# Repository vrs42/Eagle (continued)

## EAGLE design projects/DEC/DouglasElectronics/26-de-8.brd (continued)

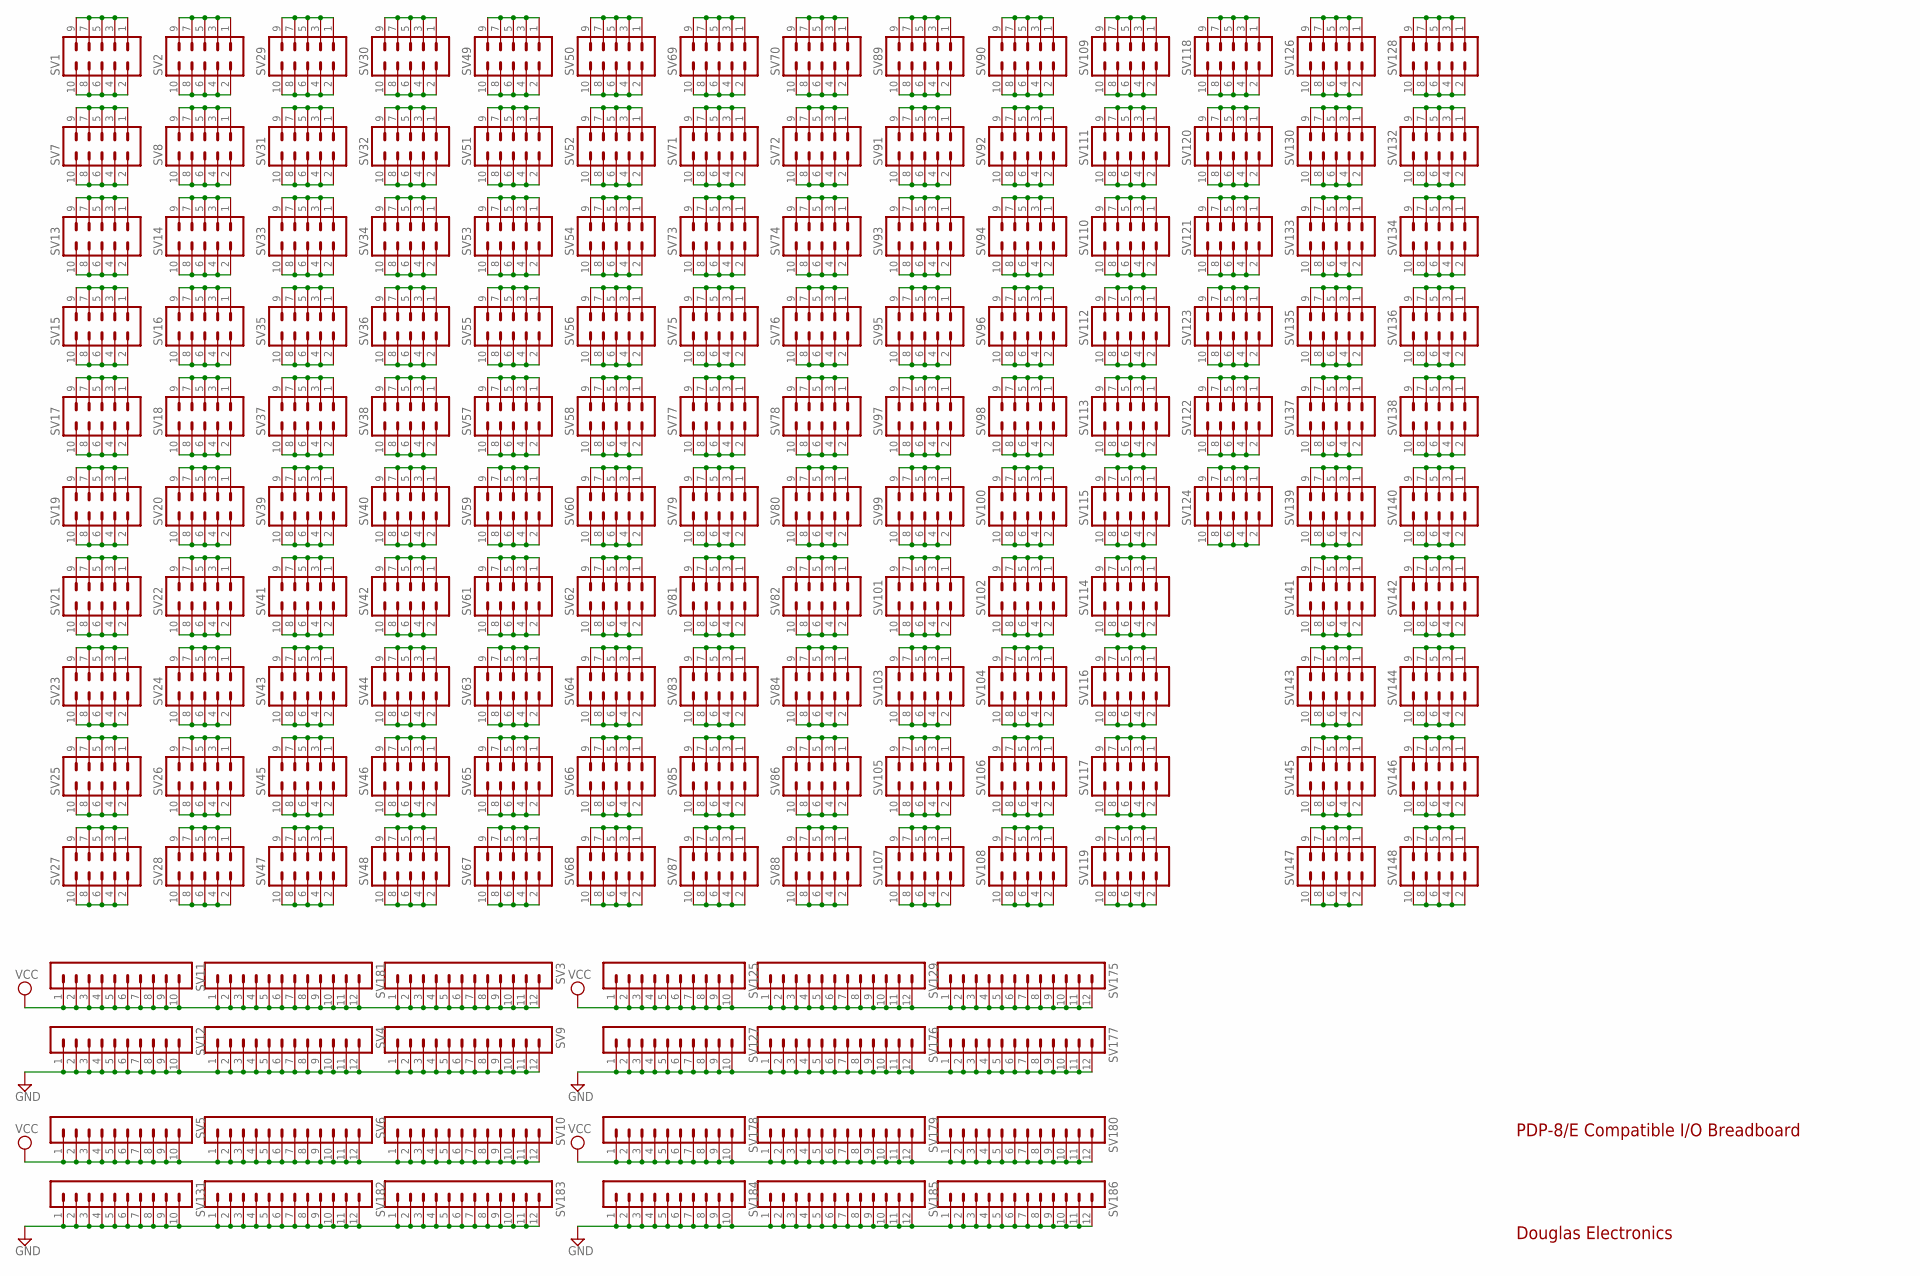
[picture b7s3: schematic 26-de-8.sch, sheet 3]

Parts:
SV1, SV2, SV7, SV8, SV13, SV14, SV15, SV16, SV17, SV18, SV19, SV20, SV21, SV22, SV23, SV24, SV25, SV26, SV27, SV28, SV29, SV30, SV31, SV32, SV33, SV34, SV35, SV36, SV37, SV38, SV39, SV40, SV41, SV42, SV43, SV44, SV45, SV46, SV47, SV48, SV49, SV50, SV51, SV52, SV53, SV54, SV55, SV56, SV57, SV58, SV59, SV60, SV61, SV62, SV63, SV64, SV65, SV66, SV67, SV68, SV69, SV70, SV71, SV72, SV73, SV74, SV75, SV76, SV77, SV78, SV79, SV80, SV81, SV82, SV83, SV84, SV85, SV86, SV87, SV88, SV89, SV90, SV91, SV92, SV93, SV94, SV95, SV96, SV97, SV98, SV99, SV100, SV101, SV102, SV103, SV104, SV105, SV106, SV107, SV108, SV109, SV110, SV111, SV112, SV113, SV114, SV115, SV116, SV117, SV118, SV119, SV120, SV121, SV122, SV123, SV124, SV126, SV128, SV130, SV132, SV133, SV134, SV135, SV136, SV137, SV138, SV139, SV140, SV141, SV142, SV143, SV144, SV145, SV146, SV147, SV148: MA05-2
SV3, SV4, SV6, SV9, SV10, SV129, SV175, SV176, SV177, SV179, SV180, SV181, SV182, SV183, SV185, SV186: MA12-1
SV5, SV11, SV12, SV125, SV127, SV131, SV178, SV184: MA10-1

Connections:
GND: SV4.1, SV4.2, SV4.3, SV4.4, SV4.5, SV4.6, SV4.7, SV4.8, SV4.9, SV4.10, SV4.11, SV4.12, SV9.1, SV9.2, SV9.3, SV9.4, SV9.5, SV9.6, SV9.7, SV9.8, SV9.9, SV9.10, SV9.11, SV9.12, SV12.1, SV12.2, SV12.3, SV12.4, SV12.5, SV12.6, SV12.7, SV12.8, SV12.9, SV12.10, SV127.1, SV127.2, SV127.3, SV127.4, SV127.5, SV127.6, SV127.7, SV127.8, SV127.9, SV127.10, SV131.1, SV131.2, SV131.3, SV131.4, SV131.5, SV131.6, SV131.7, SV131.8, SV131.9, SV131.10, SV176.1, SV176.2, SV176.3, SV176.4, SV176.5, SV176.6, SV176.7, SV176.8, SV176.9, SV176.10, SV176.11, SV176.12, SV177.1, SV177.2, SV177.3, SV177.4, SV177.5, SV177.6, SV177.7, SV177.8, SV177.9, SV177.10, SV177.11, SV177.12, SV182.1, SV182.2, SV182.3, SV182.4, SV182.5, SV182.6, SV182.7, SV182.8, SV182.9, SV182.10, SV182.11, SV182.12, SV183.1, SV183.2, SV183.3, SV183.4, SV183.5, SV183.6, SV183.7, SV183.8, SV183.9, SV183.10, SV183.11, SV183.12, SV184.1, SV184.2, SV184.3, SV184.4, SV184.5, SV184.6, SV184.7, SV184.8, SV184.9, SV184.10, SV185.1, SV185.2, SV185.3, SV185.4, SV185.5, SV185.6, SV185.7, SV185.8, SV185.9, SV185.10, SV185.11, SV185.12, SV186.1, SV186.2, SV186.3, SV186.4, SV186.5, SV186.6, SV186.7, SV186.8, SV186.9, SV186.10, SV186.11, SV186.12; also elsewhere on the board
unnamed: SV1.1, SV1.3, SV1.5, SV1.7, SV1.9
unnamed: SV1.2, SV1.4, SV1.6, SV1.8, SV1.10
unnamed: SV7.1, SV7.3, SV7.5, SV7.7, SV7.9
unnamed: SV2.1, SV2.3, SV2.5, SV2.7, SV2.9
unnamed: SV2.2, SV2.4, SV2.6, SV2.8, SV2.10
unnamed: SV7.2, SV7.4, SV7.6, SV7.8, SV7.10
unnamed: SV8.1, SV8.3, SV8.5, SV8.7, SV8.9
unnamed: SV8.2, SV8.4, SV8.6, SV8.8, SV8.10
unnamed: SV13.1, SV13.3, SV13.5, SV13.7, SV13.9
unnamed: SV13.2, SV13.4, SV13.6, SV13.8, SV13.10
unnamed: SV14.1, SV14.3, SV14.5, SV14.7, SV14.9
unnamed: SV14.2, SV14.4, SV14.6, SV14.8, SV14.10
unnamed: SV15.1, SV15.3, SV15.5, SV15.7, SV15.9
unnamed: SV15.2, SV15.4, SV15.6, SV15.8, SV15.10
unnamed: SV16.1, SV16.3, SV16.5, SV16.7, SV16.9
unnamed: SV16.2, SV16.4, SV16.6, SV16.8, SV16.10
unnamed: SV17.1, SV17.3, SV17.5, SV17.7, SV17.9
unnamed: SV17.2, SV17.4, SV17.6, SV17.8, SV17.10
unnamed: SV18.1, SV18.3, SV18.5, SV18.7, SV18.9
unnamed: SV18.2, SV18.4, SV18.6, SV18.8, SV18.10
unnamed: SV19.1, SV19.3, SV19.5, SV19.7, SV19.9
unnamed: SV19.2, SV19.4, SV19.6, SV19.8, SV19.10
unnamed: SV20.1, SV20.3, SV20.5, SV20.7, SV20.9
unnamed: SV20.2, SV20.4, SV20.6, SV20.8, SV20.10
unnamed: SV21.1, SV21.3, SV21.5, SV21.7, SV21.9
unnamed: SV21.2, SV21.4, SV21.6, SV21.8, SV21.10
unnamed: SV22.1, SV22.3, SV22.5, SV22.7, SV22.9
unnamed: SV22.2, SV22.4, SV22.6, SV22.8, SV22.10
unnamed: SV23.1, SV23.3, SV23.5, SV23.7, SV23.9
unnamed: SV23.2, SV23.4, SV23.6, SV23.8, SV23.10
unnamed: SV24.1, SV24.3, SV24.5, SV24.7, SV24.9
unnamed: SV24.2, SV24.4, SV24.6, SV24.8, SV24.10
unnamed: SV25.1, SV25.3, SV25.5, SV25.7, SV25.9
unnamed: SV25.2, SV25.4, SV25.6, SV25.8, SV25.10
unnamed: SV26.1, SV26.3, SV26.5, SV26.7, SV26.9
unnamed: SV26.2, SV26.4, SV26.6, SV26.8, SV26.10
unnamed: SV27.1, SV27.3, SV27.5, SV27.7, SV27.9
unnamed: SV27.2, SV27.4, SV27.6, SV27.8, SV27.10
unnamed: SV28.1, SV28.3, SV28.5, SV28.7, SV28.9
unnamed: SV28.2, SV28.4, SV28.6, SV28.8, SV28.10
unnamed: SV29.1, SV29.3, SV29.5, SV29.7, SV29.9
unnamed: SV29.2, SV29.4, SV29.6, SV29.8, SV29.10
unnamed: SV30.1, SV30.3, SV30.5, SV30.7, SV30.9
unnamed: SV30.2, SV30.4, SV30.6, SV30.8, SV30.10
unnamed: SV31.1, SV31.3, SV31.5, SV31.7, SV31.9
unnamed: SV31.2, SV31.4, SV31.6, SV31.8, SV31.10
unnamed: SV32.1, SV32.3, SV32.5, SV32.7, SV32.9
unnamed: SV32.2, SV32.4, SV32.6, SV32.8, SV32.10
unnamed: SV33.1, SV33.3, SV33.5, SV33.7, SV33.9
unnamed: SV33.2, SV33.4, SV33.6, SV33.8, SV33.10
unnamed: SV34.1, SV34.3, SV34.5, SV34.7, SV34.9
unnamed: SV34.2, SV34.4, SV34.6, SV34.8, SV34.10
unnamed: SV35.1, SV35.3, SV35.5, SV35.7, SV35.9
unnamed: SV35.2, SV35.4, SV35.6, SV35.8, SV35.10
unnamed: SV36.1, SV36.3, SV36.5, SV36.7, SV36.9
unnamed: SV36.2, SV36.4, SV36.6, SV36.8, SV36.10
unnamed: SV37.1, SV37.3, SV37.5, SV37.7, SV37.9
unnamed: SV37.2, SV37.4, SV37.6, SV37.8, SV37.10
unnamed: SV38.1, SV38.3, SV38.5, SV38.7, SV38.9
unnamed: SV38.2, SV38.4, SV38.6, SV38.8, SV38.10
unnamed: SV39.1, SV39.3, SV39.5, SV39.7, SV39.9
unnamed: SV39.2, SV39.4, SV39.6, SV39.8, SV39.10
unnamed: SV40.1, SV40.3, SV40.5, SV40.7, SV40.9
unnamed: SV40.2, SV40.4, SV40.6, SV40.8, SV40.10
unnamed: SV41.1, SV41.3, SV41.5, SV41.7, SV41.9
unnamed: SV41.2, SV41.4, SV41.6, SV41.8, SV41.10
unnamed: SV42.1, SV42.3, SV42.5, SV42.7, SV42.9
unnamed: SV42.2, SV42.4, SV42.6, SV42.8, SV42.10
unnamed: SV43.1, SV43.3, SV43.5, SV43.7, SV43.9
unnamed: SV43.2, SV43.4, SV43.6, SV43.8, SV43.10
unnamed: SV44.1, SV44.3, SV44.5, SV44.7, SV44.9
unnamed: SV44.2, SV44.4, SV44.6, SV44.8, SV44.10
unnamed: SV45.1, SV45.3, SV45.5, SV45.7, SV45.9
unnamed: SV45.2, SV45.4, SV45.6, SV45.8, SV45.10
unnamed: SV46.1, SV46.3, SV46.5, SV46.7, SV46.9
unnamed: SV46.2, SV46.4, SV46.6, SV46.8, SV46.10
unnamed: SV47.1, SV47.3, SV47.5, SV47.7, SV47.9
unnamed: SV47.2, SV47.4, SV47.6, SV47.8, SV47.10
unnamed: SV48.1, SV48.3, SV48.5, SV48.7, SV48.9
unnamed: SV48.2, SV48.4, SV48.6, SV48.8, SV48.10
unnamed: SV49.1, SV49.3, SV49.5, SV49.7, SV49.9
unnamed: SV49.2, SV49.4, SV49.6, SV49.8, SV49.10
unnamed: SV50.1, SV50.3, SV50.5, SV50.7, SV50.9
unnamed: SV50.2, SV50.4, SV50.6, SV50.8, SV50.10
unnamed: SV51.1, SV51.3, SV51.5, SV51.7, SV51.9
unnamed: SV51.2, SV51.4, SV51.6, SV51.8, SV51.10
unnamed: SV52.1, SV52.3, SV52.5, SV52.7, SV52.9
unnamed: SV52.2, SV52.4, SV52.6, SV52.8, SV52.10
unnamed: SV53.1, SV53.3, SV53.5, SV53.7, SV53.9
unnamed: SV53.2, SV53.4, SV53.6, SV53.8, SV53.10
unnamed: SV54.1, SV54.3, SV54.5, SV54.7, SV54.9
unnamed: SV54.2, SV54.4, SV54.6, SV54.8, SV54.10
unnamed: SV55.1, SV55.3, SV55.5, SV55.7, SV55.9
unnamed: SV55.2, SV55.4, SV55.6, SV55.8, SV55.10
unnamed: SV56.1, SV56.3, SV56.5, SV56.7, SV56.9
unnamed: SV56.2, SV56.4, SV56.6, SV56.8, SV56.10
unnamed: SV57.1, SV57.3, SV57.5, SV57.7, SV57.9
unnamed: SV57.2, SV57.4, SV57.6, SV57.8, SV57.10
unnamed: SV58.1, SV58.3, SV58.5, SV58.7, SV58.9
unnamed: SV58.2, SV58.4, SV58.6, SV58.8, SV58.10
unnamed: SV59.1, SV59.3, SV59.5, SV59.7, SV59.9
unnamed: SV59.2, SV59.4, SV59.6, SV59.8, SV59.10
unnamed: SV60.1, SV60.3, SV60.5, SV60.7, SV60.9
unnamed: SV60.2, SV60.4, SV60.6, SV60.8, SV60.10
unnamed: SV61.1, SV61.3, SV61.5, SV61.7, SV61.9
unnamed: SV61.2, SV61.4, SV61.6, SV61.8, SV61.10
unnamed: SV62.1, SV62.3, SV62.5, SV62.7, SV62.9
unnamed: SV62.2, SV62.4, SV62.6, SV62.8, SV62.10
unnamed: SV63.1, SV63.3, SV63.5, SV63.7, SV63.9
unnamed: SV63.2, SV63.4, SV63.6, SV63.8, SV63.10
unnamed: SV64.1, SV64.3, SV64.5, SV64.7, SV64.9
unnamed: SV64.2, SV64.4, SV64.6, SV64.8, SV64.10
unnamed: SV65.1, SV65.3, SV65.5, SV65.7, SV65.9
unnamed: SV65.2, SV65.4, SV65.6, SV65.8, SV65.10
unnamed: SV66.1, SV66.3, SV66.5, SV66.7, SV66.9
unnamed: SV66.2, SV66.4, SV66.6, SV66.8, SV66.10
unnamed: SV67.1, SV67.3, SV67.5, SV67.7, SV67.9
unnamed: SV67.2, SV67.4, SV67.6, SV67.8, SV67.10
unnamed: SV68.1, SV68.3, SV68.5, SV68.7, SV68.9
unnamed: SV68.2, SV68.4, SV68.6, SV68.8, SV68.10
unnamed: SV69.1, SV69.3, SV69.5, SV69.7, SV69.9
unnamed: SV69.2, SV69.4, SV69.6, SV69.8, SV69.10
unnamed: SV70.1, SV70.3, SV70.5, SV70.7, SV70.9
unnamed: SV70.2, SV70.4, SV70.6, SV70.8, SV70.10
unnamed: SV71.1, SV71.3, SV71.5, SV71.7, SV71.9
unnamed: SV71.2, SV71.4, SV71.6, SV71.8, SV71.10
unnamed: SV72.1, SV72.3, SV72.5, SV72.7, SV72.9
unnamed: SV72.2, SV72.4, SV72.6, SV72.8, SV72.10
unnamed: SV73.1, SV73.3, SV73.5, SV73.7, SV73.9
unnamed: SV73.2, SV73.4, SV73.6, SV73.8, SV73.10
unnamed: SV74.1, SV74.3, SV74.5, SV74.7, SV74.9
unnamed: SV74.2, SV74.4, SV74.6, SV74.8, SV74.10
unnamed: SV75.1, SV75.3, SV75.5, SV75.7, SV75.9
unnamed: SV75.2, SV75.4, SV75.6, SV75.8, SV75.10
unnamed: SV76.1, SV76.3, SV76.5, SV76.7, SV76.9
unnamed: SV76.2, SV76.4, SV76.6, SV76.8, SV76.10
unnamed: SV77.1, SV77.3, SV77.5, SV77.7, SV77.9
unnamed: SV77.2, SV77.4, SV77.6, SV77.8, SV77.10
unnamed: SV78.1, SV78.3, SV78.5, SV78.7, SV78.9
unnamed: SV78.2, SV78.4, SV78.6, SV78.8, SV78.10
unnamed: SV79.1, SV79.3, SV79.5, SV79.7, SV79.9
unnamed: SV79.2, SV79.4, SV79.6, SV79.8, SV79.10
unnamed: SV80.1, SV80.3, SV80.5, SV80.7, SV80.9
unnamed: SV80.2, SV80.4, SV80.6, SV80.8, SV80.10
unnamed: SV81.1, SV81.3, SV81.5, SV81.7, SV81.9
unnamed: SV81.2, SV81.4, SV81.6, SV81.8, SV81.10
unnamed: SV82.1, SV82.3, SV82.5, SV82.7, SV82.9
unnamed: SV82.2, SV82.4, SV82.6, SV82.8, SV82.10
unnamed: SV83.1, SV83.3, SV83.5, SV83.7, SV83.9
unnamed: SV83.2, SV83.4, SV83.6, SV83.8, SV83.10
unnamed: SV84.1, SV84.3, SV84.5, SV84.7, SV84.9
unnamed: SV84.2, SV84.4, SV84.6, SV84.8, SV84.10
unnamed: SV85.1, SV85.3, SV85.5, SV85.7, SV85.9
unnamed: SV85.2, SV85.4, SV85.6, SV85.8, SV85.10
unnamed: SV86.1, SV86.3, SV86.5, SV86.7, SV86.9
unnamed: SV86.2, SV86.4, SV86.6, SV86.8, SV86.10
unnamed: SV87.1, SV87.3, SV87.5, SV87.7, SV87.9
unnamed: SV87.2, SV87.4, SV87.6, SV87.8, SV87.10
unnamed: SV88.1, SV88.3, SV88.5, SV88.7, SV88.9
unnamed: SV88.2, SV88.4, SV88.6, SV88.8, SV88.10
unnamed: SV89.1, SV89.3, SV89.5, SV89.7, SV89.9
unnamed: SV89.2, SV89.4, SV89.6, SV89.8, SV89.10
unnamed: SV90.1, SV90.3, SV90.5, SV90.7, SV90.9
unnamed: SV90.2, SV90.4, SV90.6, SV90.8, SV90.10
unnamed: SV91.1, SV91.3, SV91.5, SV91.7, SV91.9
unnamed: SV91.2, SV91.4, SV91.6, SV91.8, SV91.10
unnamed: SV92.1, SV92.3, SV92.5, SV92.7, SV92.9
unnamed: SV92.2, SV92.4, SV92.6, SV92.8, SV92.10
unnamed: SV93.1, SV93.3, SV93.5, SV93.7, SV93.9
unnamed: SV93.2, SV93.4, SV93.6, SV93.8, SV93.10
unnamed: SV94.1, SV94.3, SV94.5, SV94.7, SV94.9
unnamed: SV94.2, SV94.4, SV94.6, SV94.8, SV94.10
unnamed: SV95.1, SV95.3, SV95.5, SV95.7, SV95.9
unnamed: SV95.2, SV95.4, SV95.6, SV95.8, SV95.10
unnamed: SV96.1, SV96.3, SV96.5, SV96.7, SV96.9
unnamed: SV96.2, SV96.4, SV96.6, SV96.8, SV96.10
unnamed: SV97.1, SV97.3, SV97.5, SV97.7, SV97.9
unnamed: SV97.2, SV97.4, SV97.6, SV97.8, SV97.10
unnamed: SV98.1, SV98.3, SV98.5, SV98.7, SV98.9
unnamed: SV98.2, SV98.4, SV98.6, SV98.8, SV98.10
unnamed: SV99.1, SV99.3, SV99.5, SV99.7, SV99.9
unnamed: SV99.2, SV99.4, SV99.6, SV99.8, SV99.10
unnamed: SV100.1, SV100.3, SV100.5, SV100.7, SV100.9
unnamed: SV100.2, SV100.4, SV100.6, SV100.8, SV100.10
unnamed: SV101.1, SV101.3, SV101.5, SV101.7, SV101.9
unnamed: SV101.2, SV101.4, SV101.6, SV101.8, SV101.10
unnamed: SV102.1, SV102.3, SV102.5, SV102.7, SV102.9
unnamed: SV102.2, SV102.4, SV102.6, SV102.8, SV102.10
unnamed: SV103.1, SV103.3, SV103.5, SV103.7, SV103.9
unnamed: SV103.2, SV103.4, SV103.6, SV103.8, SV103.10
unnamed: SV104.1, SV104.3, SV104.5, SV104.7, SV104.9
unnamed: SV104.2, SV104.4, SV104.6, SV104.8, SV104.10
unnamed: SV105.1, SV105.3, SV105.5, SV105.7, SV105.9
unnamed: SV105.2, SV105.4, SV105.6, SV105.8, SV105.10
unnamed: SV106.1, SV106.3, SV106.5, SV106.7, SV106.9
unnamed: SV106.2, SV106.4, SV106.6, SV106.8, SV106.10
unnamed: SV107.1, SV107.3, SV107.5, SV107.7, SV107.9
unnamed: SV107.2, SV107.4, SV107.6, SV107.8, SV107.10
unnamed: SV108.1, SV108.3, SV108.5, SV108.7, SV108.9
unnamed: SV108.2, SV108.4, SV108.6, SV108.8, SV108.10
unnamed: SV109.1, SV109.3, SV109.5, SV109.7, SV109.9
unnamed: SV109.2, SV109.4, SV109.6, SV109.8, SV109.10
unnamed: SV110.1, SV110.3, SV110.5, SV110.7, SV110.9
unnamed: SV110.2, SV110.4, SV110.6, SV110.8, SV110.10
unnamed: SV111.1, SV111.3, SV111.5, SV111.7, SV111.9
unnamed: SV111.2, SV111.4, SV111.6, SV111.8, SV111.10
unnamed: SV112.1, SV112.3, SV112.5, SV112.7, SV112.9
unnamed: SV112.2, SV112.4, SV112.6, SV112.8, SV112.10
unnamed: SV113.1, SV113.3, SV113.5, SV113.7, SV113.9
unnamed: SV113.2, SV113.4, SV113.6, SV113.8, SV113.10
unnamed: SV114.1, SV114.3, SV114.5, SV114.7, SV114.9
unnamed: SV114.2, SV114.4, SV114.6, SV114.8, SV114.10
unnamed: SV115.1, SV115.3, SV115.5, SV115.7, SV115.9
unnamed: SV115.2, SV115.4, SV115.6, SV115.8, SV115.10
unnamed: SV116.1, SV116.3, SV116.5, SV116.7, SV116.9
unnamed: SV116.2, SV116.4, SV116.6, SV116.8, SV116.10
unnamed: SV117.1, SV117.3, SV117.5, SV117.7, SV117.9
unnamed: SV117.2, SV117.4, SV117.6, SV117.8, SV117.10
unnamed: SV118.1, SV118.3, SV118.5, SV118.7, SV118.9
unnamed: SV118.2, SV118.4, SV118.6, SV118.8, SV118.10
unnamed: SV119.1, SV119.3, SV119.5, SV119.7, SV119.9
unnamed: SV119.2, SV119.4, SV119.6, SV119.8, SV119.10
unnamed: SV120.1, SV120.3, SV120.5, SV120.7, SV120.9
unnamed: SV120.2, SV120.4, SV120.6, SV120.8, SV120.10
unnamed: SV121.1, SV121.3, SV121.5, SV121.7, SV121.9
unnamed: SV121.2, SV121.4, SV121.6, SV121.8, SV121.10
unnamed: SV122.1, SV122.3, SV122.5, SV122.7, SV122.9
unnamed: SV122.2, SV122.4, SV122.6, SV122.8, SV122.10
unnamed: SV123.1, SV123.3, SV123.5, SV123.7, SV123.9
unnamed: SV123.2, SV123.4, SV123.6, SV123.8, SV123.10
unnamed: SV124.1, SV124.3, SV124.5, SV124.7, SV124.9
unnamed: SV124.2, SV124.4, SV124.6, SV124.8, SV124.10
unnamed: SV126.1, SV126.3, SV126.5, SV126.7, SV126.9
unnamed: SV126.2, SV126.4, SV126.6, SV126.8, SV126.10
unnamed: SV128.1, SV128.3, SV128.5, SV128.7, SV128.9
unnamed: SV128.2, SV128.4, SV128.6, SV128.8, SV128.10
unnamed: SV130.1, SV130.3, SV130.5, SV130.7, SV130.9
unnamed: SV130.2, SV130.4, SV130.6, SV130.8, SV130.10
unnamed: SV132.1, SV132.3, SV132.5, SV132.7, SV132.9
unnamed: SV132.2, SV132.4, SV132.6, SV132.8, SV132.10
unnamed: SV133.1, SV133.3, SV133.5, SV133.7, SV133.9
unnamed: SV133.2, SV133.4, SV133.6, SV133.8, SV133.10
unnamed: SV134.1, SV134.3, SV134.5, SV134.7, SV134.9
unnamed: SV134.2, SV134.4, SV134.6, SV134.8, SV134.10
unnamed: SV135.1, SV135.3, SV135.5, SV135.7, SV135.9
unnamed: SV135.2, SV135.4, SV135.6, SV135.8, SV135.10
unnamed: SV136.1, SV136.3, SV136.5, SV136.7, SV136.9
unnamed: SV136.2, SV136.4, SV136.6, SV136.8, SV136.10
unnamed: SV137.1, SV137.3, SV137.5, SV137.7, SV137.9
unnamed: SV137.2, SV137.4, SV137.6, SV137.8, SV137.10
unnamed: SV138.1, SV138.3, SV138.5, SV138.7, SV138.9
unnamed: SV138.2, SV138.4, SV138.6, SV138.8, SV138.10
unnamed: SV139.1, SV139.3, SV139.5, SV139.7, SV139.9
unnamed: SV139.2, SV139.4, SV139.6, SV139.8, SV139.10
unnamed: SV140.1, SV140.3, SV140.5, SV140.7, SV140.9
unnamed: SV140.2, SV140.4, SV140.6, SV140.8, SV140.10
unnamed: SV141.1, SV141.3, SV141.5, SV141.7, SV141.9
unnamed: SV141.2, SV141.4, SV141.6, SV141.8, SV141.10
unnamed: SV142.1, SV142.3, SV142.5, SV142.7, SV142.9
unnamed: SV142.2, SV142.4, SV142.6, SV142.8, SV142.10
unnamed: SV143.1, SV143.3, SV143.5, SV143.7, SV143.9
unnamed: SV143.2, SV143.4, SV143.6, SV143.8, SV143.10
unnamed: SV144.1, SV144.3, SV144.5, SV144.7, SV144.9
unnamed: SV144.2, SV144.4, SV144.6, SV144.8, SV144.10
unnamed: SV145.1, SV145.3, SV145.5, SV145.7, SV145.9
unnamed: SV145.2, SV145.4, SV145.6, SV145.8, SV145.10
unnamed: SV146.1, SV146.3, SV146.5, SV146.7, SV146.9
unnamed: SV146.2, SV146.4, SV146.6, SV146.8, SV146.10
unnamed: SV147.1, SV147.3, SV147.5, SV147.7, SV147.9
unnamed: SV147.2, SV147.4, SV147.6, SV147.8, SV147.10
unnamed: SV148.1, SV148.3, SV148.5, SV148.7, SV148.9
unnamed: SV148.2, SV148.4, SV148.6, SV148.8, SV148.10
VCC: SV3.1, SV3.2, SV3.3, SV3.4, SV3.5, SV3.6, SV3.7, SV3.8, SV3.9, SV3.10, SV3.11, SV3.12, SV5.1, SV5.2, SV5.3, SV5.4, SV5.5, SV5.6, SV5.7, SV5.8, SV5.9, SV5.10, SV6.1, SV6.2, SV6.3, SV6.4, SV6.5, SV6.6, SV6.7, SV6.8, SV6.9, SV6.10, SV6.11, SV6.12, SV10.1, SV10.2, SV10.3, SV10.4, SV10.5, SV10.6, SV10.7, SV10.8, SV10.9, SV10.10, SV10.11, SV10.12, SV11.1, SV11.2, SV11.3, SV11.4, SV11.5, SV11.6, SV11.7, SV11.8, SV11.9, SV11.10, SV125.1, SV125.2, SV125.3, SV125.4, SV125.5, SV125.6, SV125.7, SV125.8, SV125.9, SV125.10, SV129.1, SV129.2, SV129.3, SV129.4, SV129.5, SV129.6, SV129.7, SV129.8, SV129.9, SV129.10, SV129.11, SV129.12, SV175.1, SV175.2, SV175.3, SV175.4, SV175.5, SV175.6, SV175.7, SV175.8, SV175.9, SV175.10, SV175.11, SV175.12, SV178.1, SV178.2, SV178.3, SV178.4, SV178.5, SV178.6, SV178.7, SV178.8, SV178.9, SV178.10, SV179.1, SV179.2, SV179.3, SV179.4, SV179.5, SV179.6, SV179.7, SV179.8, SV179.9, SV179.10, SV179.11, SV179.12, SV180.1, SV180.2, SV180.3, SV180.4, SV180.5, SV180.6, SV180.7, SV180.8, SV180.9, SV180.10, SV180.11, SV180.12, SV181.1, SV181.2, SV181.3, SV181.4, SV181.5, SV181.6, SV181.7, SV181.8, SV181.9, SV181.10, SV181.11, SV181.12; also elsewhere on the board

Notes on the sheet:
PDP-8/E Compatible I/O Breadboard
Douglas Electronics
